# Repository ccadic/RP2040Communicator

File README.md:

# RP2040Communicator
4 cm x 4 cm small communicator

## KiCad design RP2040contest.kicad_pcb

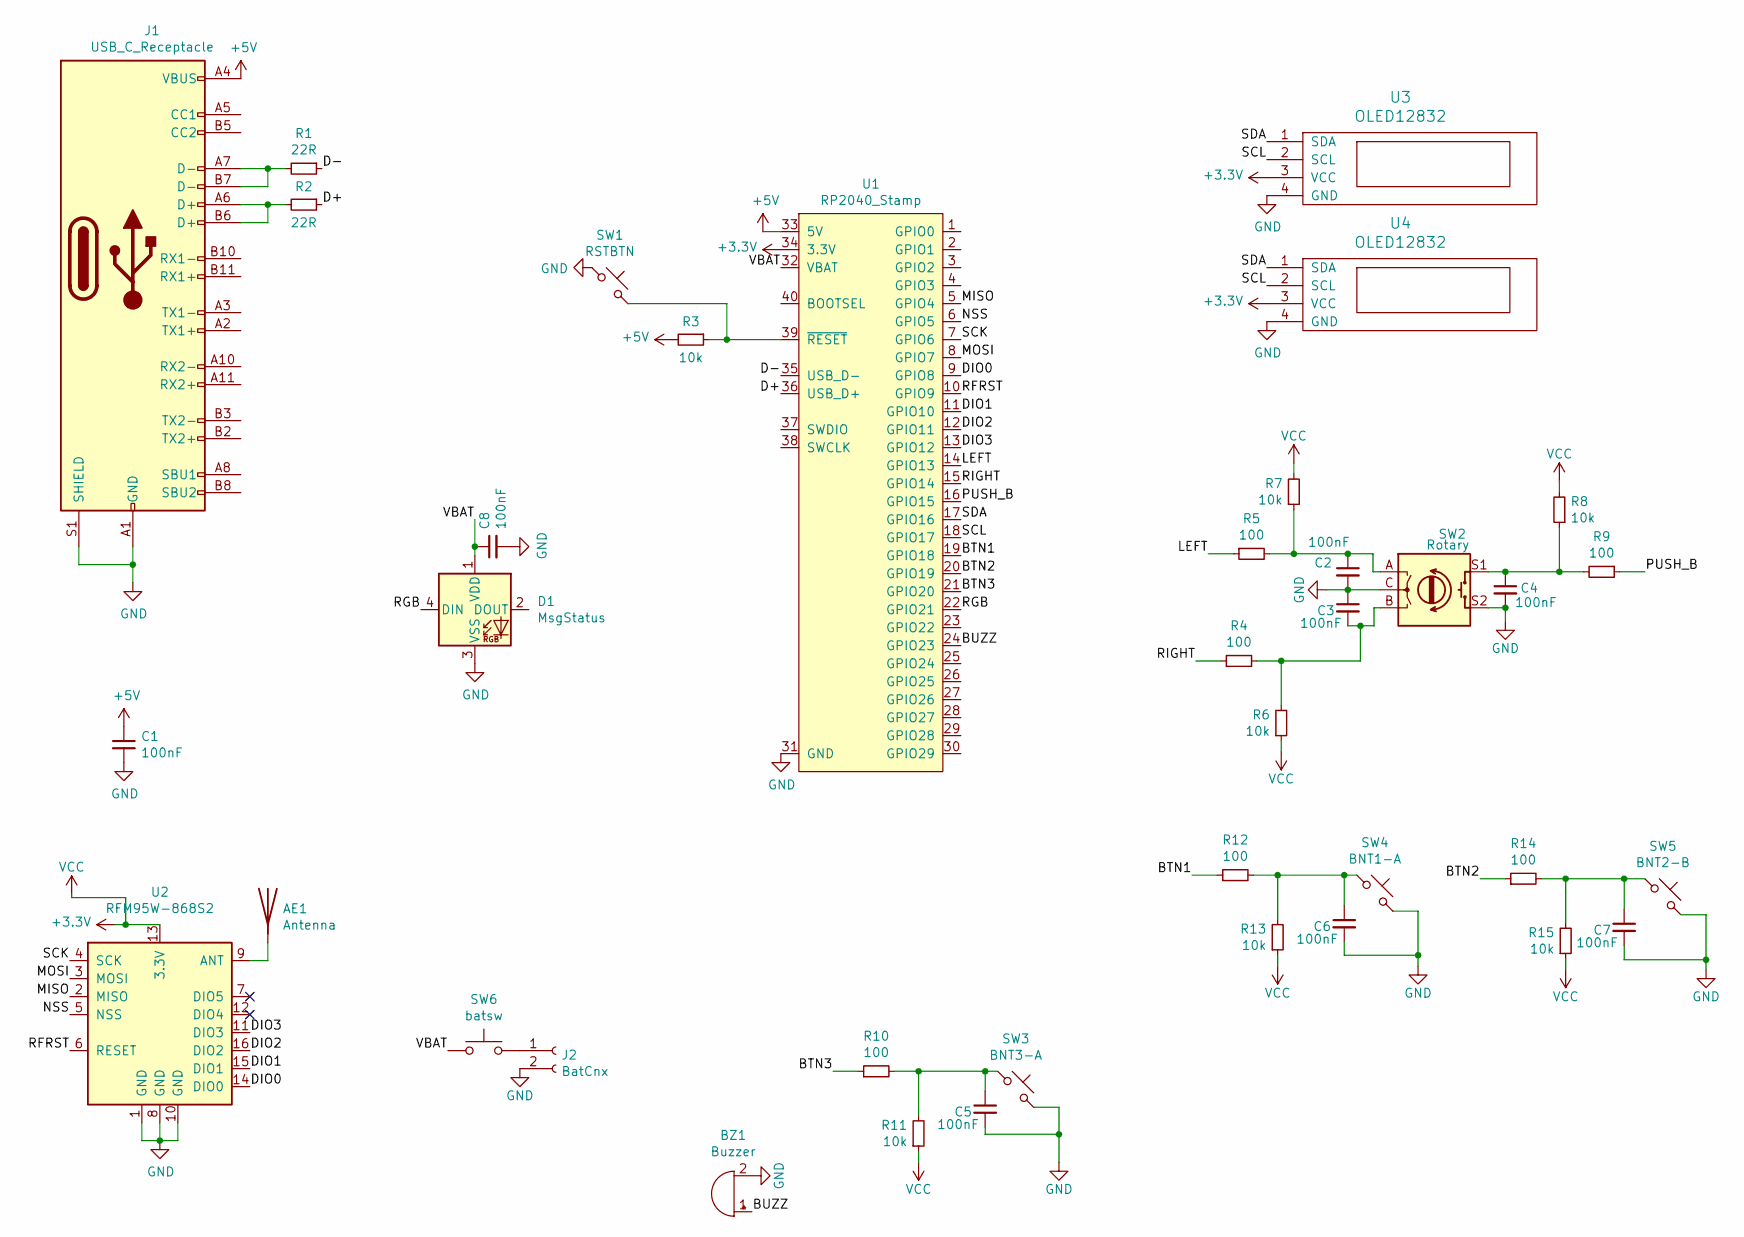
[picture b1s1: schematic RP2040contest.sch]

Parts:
AE1: Antenna; U.FL_Molex_MCRF_73412-0110_Vertical
BZ1: Buzzer; Buzzer93
C1, C8: 100nF; C_0603_1608Metric
C2, C3, C4, C5, C6, C7: 100nF; C_0402_1005Metric
D1: MsgStatus; LED_WS2812B_PLCC4_5.0x5.0mm_P3.2mm
J1: USB_C_Receptacle; GT-USB-7010
J2: BatCnx; 2pads
R1, R2: 22R; R_0603_1608Metric
R3, R11, R13, R15: 10k; R_0603_1608Metric
R4, R5, R9: 100; R_0402_1005Metric
R6, R7, R8: 10k; R_0402_1005Metric
R10, R12, R14: 100; R_0603_1608Metric
SW1: RSTBTN; SW_SPST_B3U-1000P-B
SW2: Rotary; RotaryEncoder_Alps_EC11E-Switch_Vertical_H20mm
SW3: BNT3-A; SW_TP1003
SW4: BNT1-A; SW_TP1003
SW5: BNT2-B; SW_TP1003
SW6: batsw; PinHeader_1x02_P2.00mm_Vertical
U1: RP2040_Stamp; RP2040_Stamp_SMD
U2: RFM95W-868S2; RFM95W_long
U3, U4: OLED12832; OLED-0.91-128x32

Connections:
+3V3: R6.1, R7.2, R8.2, R11.1, R13.1, R15.1, U1.34 (3.3V), U2.13 (3.3V), U3.3 (VCC), U4.3 (VCC)
+5V: C1.1, J1.A4 (VBUS), J1.A9 (VBUS), J1.B4 (VBUS), J1.B9 (VBUS), R3.2, U1.33 (5V)
/BTN1: R12.1, U1.19 (GPIO18)
/BTN2: R14.1, U1.20 (GPIO19)
/BTN3: R10.1, U1.21 (GPIO20)
/BUZZ: BZ1.1 (-), U1.24 (GPIO23)
/D+: R2.1, U1.36 (USB_D+)
/D-: R1.1, U1.35 (USB_D-)
/DIO0: U1.9 (GPIO8), U2.14 (DIO0)
/DIO1: U1.11 (GPIO10), U2.15 (DIO1)
/DIO2: U1.12 (GPIO11), U2.16 (DIO2)
/DIO3: U1.13 (GPIO12), U2.11 (DIO3)
/LEFT: R5.1, U1.14 (GPIO13)
/MISO: U1.5 (GPIO4), U2.2 (MISO)
/MOSI: U1.8 (GPIO7), U2.3 (MOSI)
/NSS: U1.6 (GPIO5), U2.5 (NSS)
/PUSH_B: R9.1, U1.16 (GPIO15)
/RFRST: U1.10 (GPIO9), U2.6 (RESET)
/RGB: D1.4 (DIN), U1.22 (GPIO21)
/RIGHT: R4.1, U1.15 (GPIO14)
/SCK: U1.7 (GPIO6), U2.4 (SCK)
/SCL: U1.18 (GPIO17), U3.2 (SCL), U4.2 (SCL)
/SDA: U1.17 (GPIO16), U3.1 (SDA), U4.1 (SDA)
/VBAT: C8.1, D1.1 (VDD), SW6.1, U1.32 (VBAT)
GND: BZ1.2 (+), C1.2, C2.2, C3.1, C4.2, C5.2, C6.2, C7.2, C8.2, D1.3 (VSS), J1.A1 (GND), J1.A12 (GND), J1.B1 (GND), J1.B12 (GND), J1.S1 (SHIELD), J2.2, SW1.1, SW2.C, SW2.S2, SW3.2, SW4.2, SW5.2, U1.31 (GND), U2.1 (GND), U2.8 (GND), U2.10 (GND), U3.4 (GND), U4.4 (GND)
unnamed: AE1.1, U2.9 (ANT)
unnamed: C2.1, R5.2, R7.1, SW2.A
unnamed: C3.2, R4.2, R6.2, SW2.B
unnamed: C4.1, R8.1, R9.2, SW2.S1
unnamed: C5.1, R10.2, R11.2, SW3.1
unnamed: C6.1, R12.2, R13.2, SW4.1
unnamed: C7.1, R14.2, R15.2, SW5.1
unnamed: J1.A6 (D+), J1.B6 (D+), R2.2
unnamed: J1.A7 (D-), J1.B7 (D-), R1.2
unnamed: J2.1, SW6.2
unnamed: R3.1, SW1.2, U1.39 (~RESET)

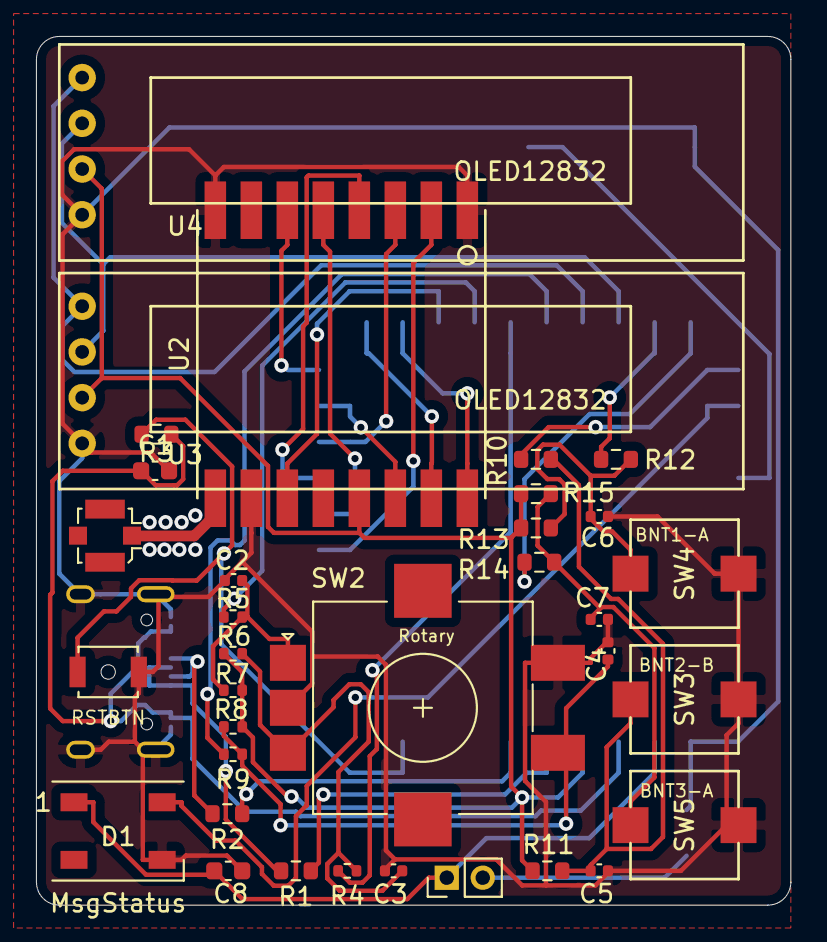
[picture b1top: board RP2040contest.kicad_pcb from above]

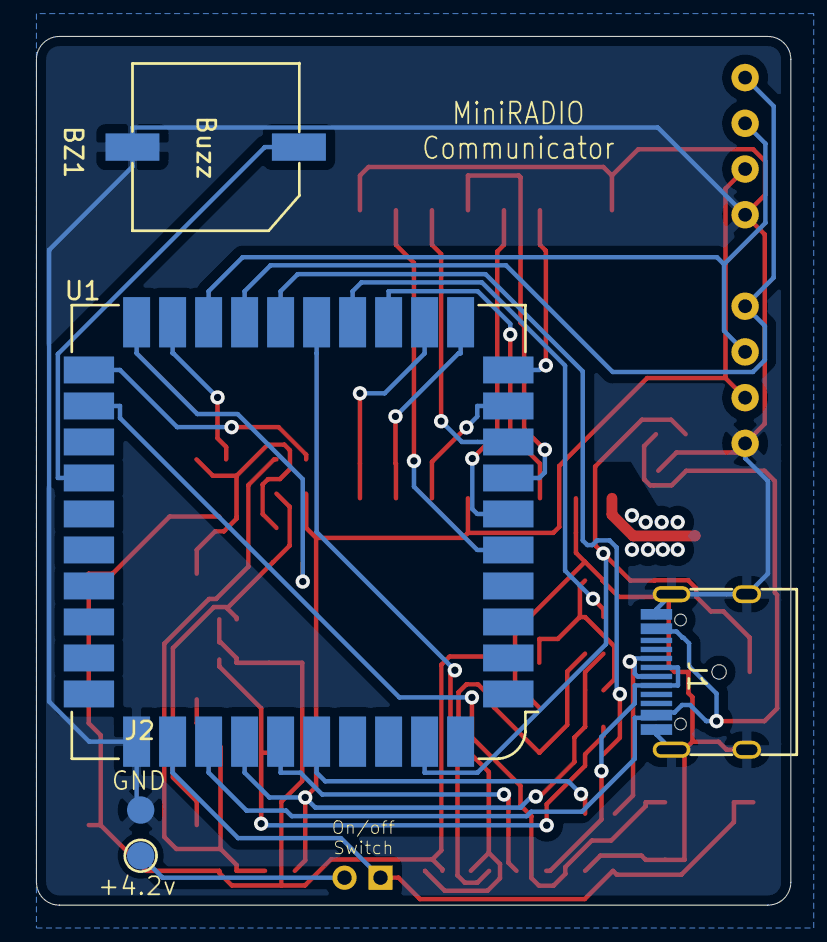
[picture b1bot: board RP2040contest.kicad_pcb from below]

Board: 2 copper layers, 41.9 x 48.3 mm, 38 parts (4 on the bottom side), 36 nets.
